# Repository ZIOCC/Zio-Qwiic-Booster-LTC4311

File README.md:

# Zio Qwiic Booster (LTC4311)

> This product can be available for purchase [here](https://www.smart-prototyping.com/Zio-Qwiic-Booster.html).

#### Description

The ZIO Qwiic Booster is a breakout for the Linear Technology LTC4311. 

The LTC4311 is a low-voltage I2C bus accelerator, dramatically reducing the transition times of the SDA and SCL signals, and enabling reliable operation of I2C interconnects over much longer cable runs than normally possible.

If you need to place your Qwiic sensor or actuator driver more than a couple of meters away from your MCU, consider using this board to ensure reliable operation. If you use Qwiic boards, or any I2C boards for that matter, in your interactive installations or other experimental hardware builds, we highly recommend having at least one of these little life-savers in your box of tricks.

#### Specification

* Dimension: 14.3x 26.5mm
* IC: LTC4311

#### Links

* [LTC4311 Datasheet](http://www.analog.com/media/en/technical-documentation/data-sheets/4311fa.pdf)

> ###### About Zio
> Zio is a new line of open sourced, compact, and grid layout boards, fully integrated for Arduino and Qwiic ecosystem. Designed ideally for wearables, robotics, small-space limitations or other on the go projects. Check out other awesome Zio products [here](https://www.smart-prototyping.com/Zio).

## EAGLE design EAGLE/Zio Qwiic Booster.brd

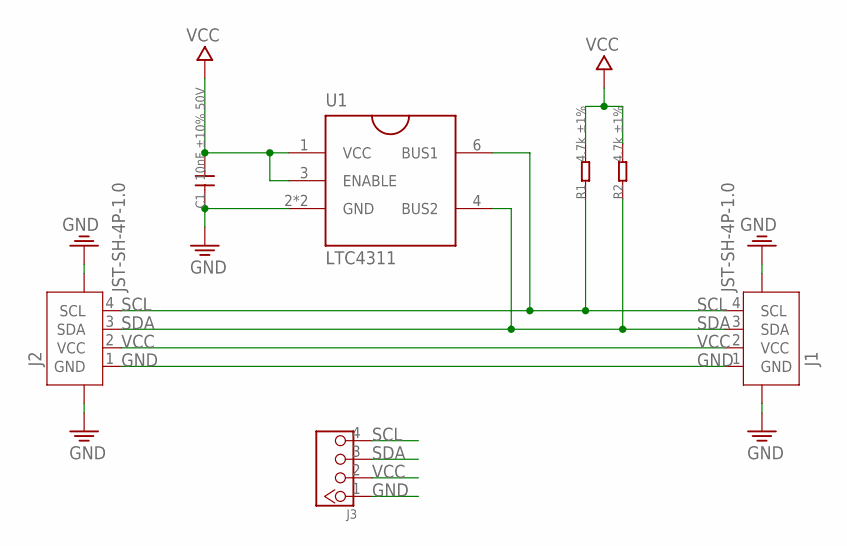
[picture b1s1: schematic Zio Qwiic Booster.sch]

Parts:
C1: 10nF ±10% 50V; 0603
J1, J2: JST-SH-4P-1.0; JST-SH-4P
J3: HEADER-4P-60/35MIL; 4P-65/35MIL
R1, R2: 4.7k ±1%; 0603
U1: LTC4311; SC70-6L

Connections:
GND: C1.1, J1.1 (GND), J1.NC1 (5), J1.NC2 (6), J2.1 (GND), J2.NC1 (5), J2.NC2 (6), J3.1, U1.2 (GND), U1.5 (GND)
SCL: J1.4 (SCL), J2.4 (SCL), J3.4, R1.1, U1.6 (BUS1)
SDA: J1.3 (SDA), J2.3 (SDA), J3.3, R2.1, U1.4 (BUS2)
VCC: C1.2, J1.2 (VCC), J2.2 (VCC), J3.2, R1.2, R2.2, U1.1 (VCC), U1.3 (ENABLE)

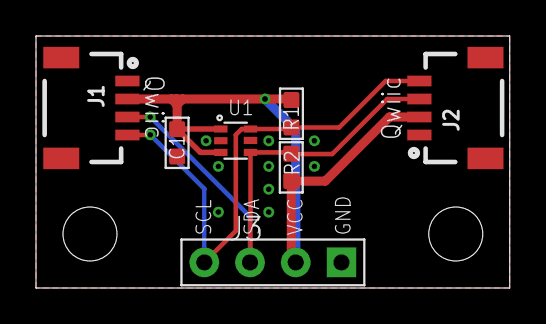
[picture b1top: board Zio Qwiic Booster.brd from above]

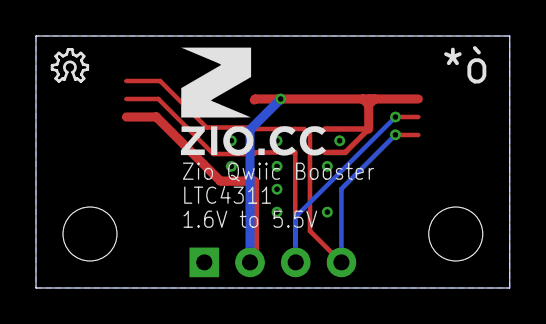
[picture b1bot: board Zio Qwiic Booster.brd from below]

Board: 2 copper layers, 26.3 x 14.0 mm, 9 parts (2 on the bottom side), 4 nets.

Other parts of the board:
U$3: 6MM
U$4: OSHW_6X70_NOTEXT
